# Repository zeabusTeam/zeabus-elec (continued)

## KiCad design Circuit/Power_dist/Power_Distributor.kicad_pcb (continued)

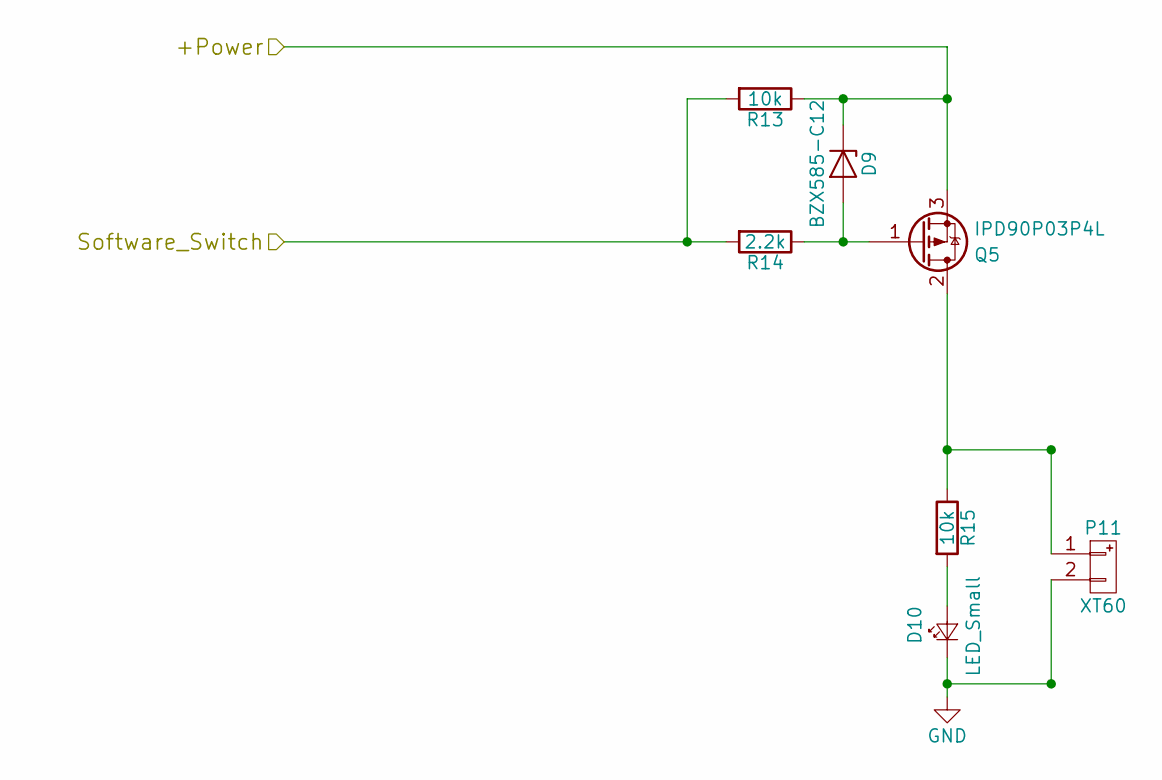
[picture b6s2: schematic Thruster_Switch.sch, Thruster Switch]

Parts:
D1: BZX585-C12; D_SOD-523
D2: LED_Small; LED_0603
P1: XT60
Q1: IPD90P03P4L; TO-252-2
R1, R3: 10k; R_0603
R2: 2.2k; R_0603

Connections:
+BATT: D1.1 (K), Q1.3 (S), R1.1; also elsewhere on the board
/Power_Controller/SW2_C: R1.2, R2.2; also elsewhere on the board
GND: D2.1 (K), P1.2; also elsewhere on the board
unnamed: D1.2 (A), Q1.1 (G), R2.1
unnamed: D2.2 (A), R3.2
unnamed: P1.1, Q1.2 (D), R3.1

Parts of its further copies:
D9: BZX585-C12; D_SOD-523
D10: LED_Small; LED_0603
P7, P11: XT60
Q4, Q5: IPD90P03P4L; TO-252-2
R13, R15: 10k; R_0603
R14: 2.2k; R_0603

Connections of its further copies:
+BATT: D9.1 (K), Q5.3 (S), R13.1; also elsewhere on the board
/Power_Controller/SW1_C: R13.2, R14.2; also elsewhere on the board
GND: D10.1 (K), P11.2; also elsewhere on the board
unnamed: D9.2 (A), Q5.1 (G), R14.1
unnamed: D10.2 (A), R15.2
unnamed: P11.1, Q5.2 (D), R15.1

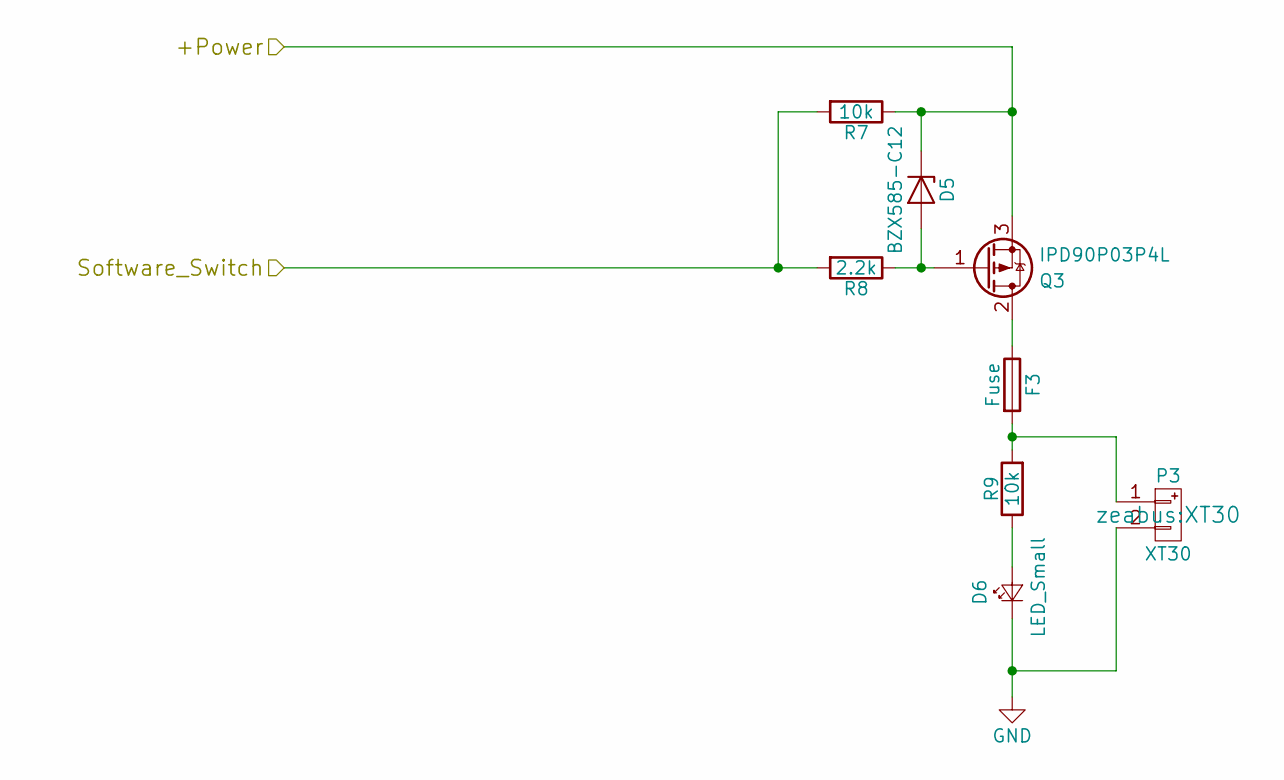
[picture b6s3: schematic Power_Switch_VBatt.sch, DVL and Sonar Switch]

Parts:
D3: BZX585-C12; D_SOD-523
D4: LED_Small; LED_0603_HandSoldering
F2: Fuse; FUSE_AUTO
P2: XT30
Q2: IPD90P03P4L; TO-252-2
R4, R6: 10k; R_0603
R5: 2.2k; R_0603

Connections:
+BATT: D3.1 (K), Q2.3 (S), R4.1; also elsewhere on the board
/Power_Controller/SW3_C: R4.2, R5.2; also elsewhere on the board
GND: D4.1 (K), P2.2; also elsewhere on the board
unnamed: D3.2 (A), Q2.1 (G), R5.1
unnamed: D4.2 (A), R6.1
unnamed: F2.1, Q2.2 (D)
unnamed: F2.2, P2.1, R6.2

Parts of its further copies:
D5: BZX585-C12; D_SOD-523
D6: LED_Small; LED_0603_HandSoldering
F3: Fuse; FUSE_AUTO
P3: XT30
Q3: IPD90P03P4L; TO-252-2
R7, R9: 10k; R_0603
R8: 2.2k; R_0603

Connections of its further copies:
+BATT: D5.1 (K), Q3.3 (S), R7.1; also elsewhere on the board
/Power_Controller/SW4_C: R7.2, R8.2; also elsewhere on the board
GND: D6.1 (K), P3.2; also elsewhere on the board
unnamed: D5.2 (A), Q3.1 (G), R8.1
unnamed: D6.2 (A), R9.1
unnamed: F3.1, Q3.2 (D)
unnamed: F3.2, P3.1, R9.2

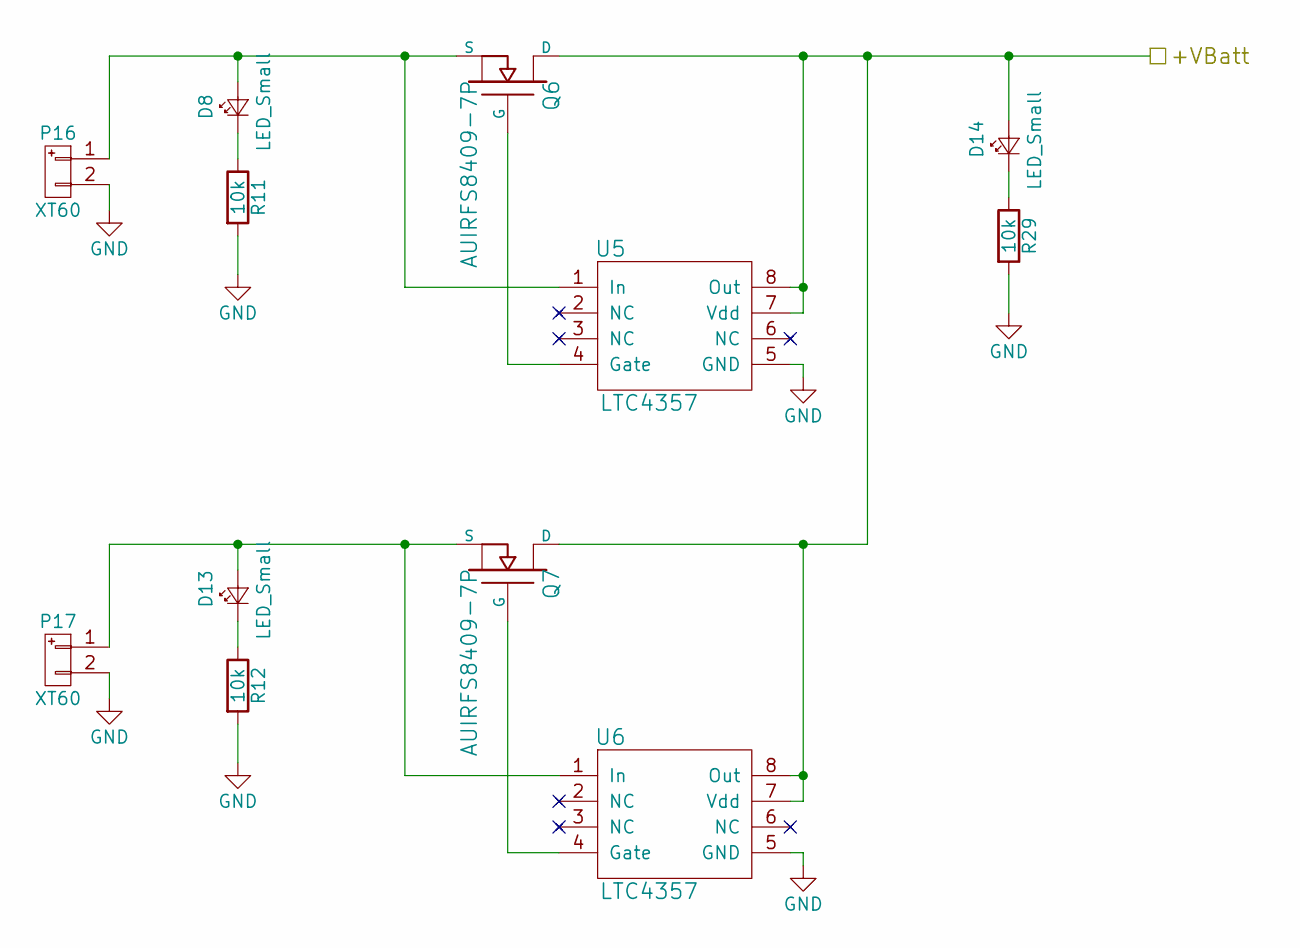
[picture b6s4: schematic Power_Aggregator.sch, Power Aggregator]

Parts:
D8, D13, D14: LED_Small; LED_0603_HandSoldering
P16, P17: XT60
Q6, Q7: AUIRFS8409-7P; D2PAK-7
R11, R12, R29: 10k; R_0603_HandSoldering
U5, U6: LTC4357; MSOP-8_3x3mm_Pitch0.65mm

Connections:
+BATT: D14.2 (A), Q6.D, Q7.D, U5.7 (Vdd), U5.8 (Out), U6.7 (Vdd), U6.8 (Out); also elsewhere on the board
GND: P16.2, P17.2, R11.2, R12.2, R29.2, U5.5 (GND), U6.5 (GND); also elsewhere on the board
unnamed: D8.1 (K), R11.1
unnamed: D8.2 (A), P16.1, Q6.S, U5.1 (In)
unnamed: D13.1 (K), R12.1
unnamed: D13.2 (A), P17.1, Q7.S, U6.1 (In)
unnamed: D14.1 (K), R29.1
unnamed: Q6.G, U5.4 (Gate)
unnamed: Q7.G, U6.4 (Gate)

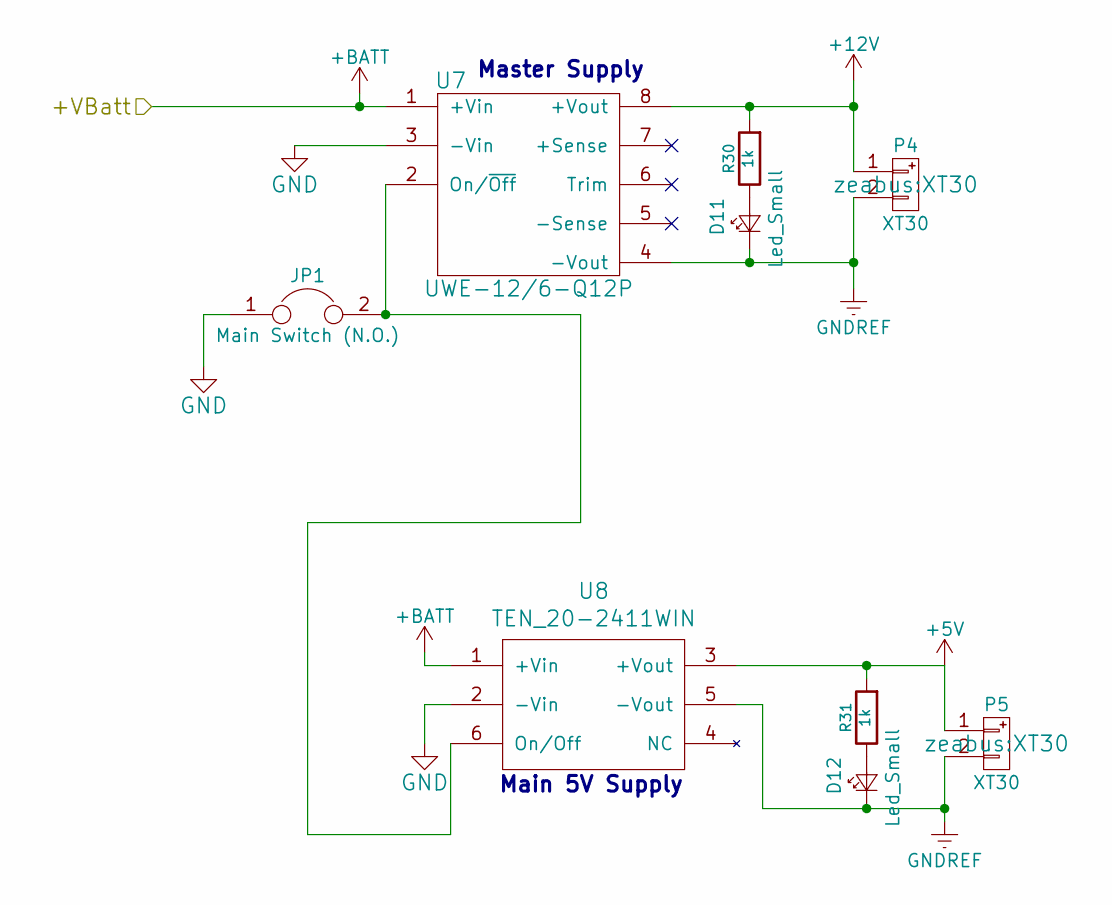
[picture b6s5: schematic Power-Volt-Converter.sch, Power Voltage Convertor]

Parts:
D11, D12: Led_Small; LED_0603_HandSoldering
JP1: Main Switch (N.O.); Pin_Header_Straight_1x02_Pitch2.54mm
P4, P5: XT30
R30, R31: 1k; R_0603_HandSoldering
U7: UWE-12/6-Q12P; UWE-xxxx
U8: TEN_20-2411WIN; TEN_20WIN

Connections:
+5V: P5.1, R31.2, U8.3 (+Vout); also elsewhere on the board
+12V: P4.1, R30.2, U7.8 (+Vout); also elsewhere on the board
+BATT: U7.1 (+Vin), U8.1 (+Vin); also elsewhere on the board
GND: JP1.1, U7.3 (-Vin), U8.2 (-Vin); also elsewhere on the board
GNDREF: D11.1 (K), D12.1 (K), P4.2, P5.2, U7.4 (-Vout), U8.5 (-Vout); also elsewhere on the board
unnamed: D11.2 (A), R30.1
unnamed: D12.2 (A), R31.1
unnamed: JP1.2, U7.2 (On/~Off), U8.6 (On/Off)

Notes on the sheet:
Master Supply
Main 5V Supply

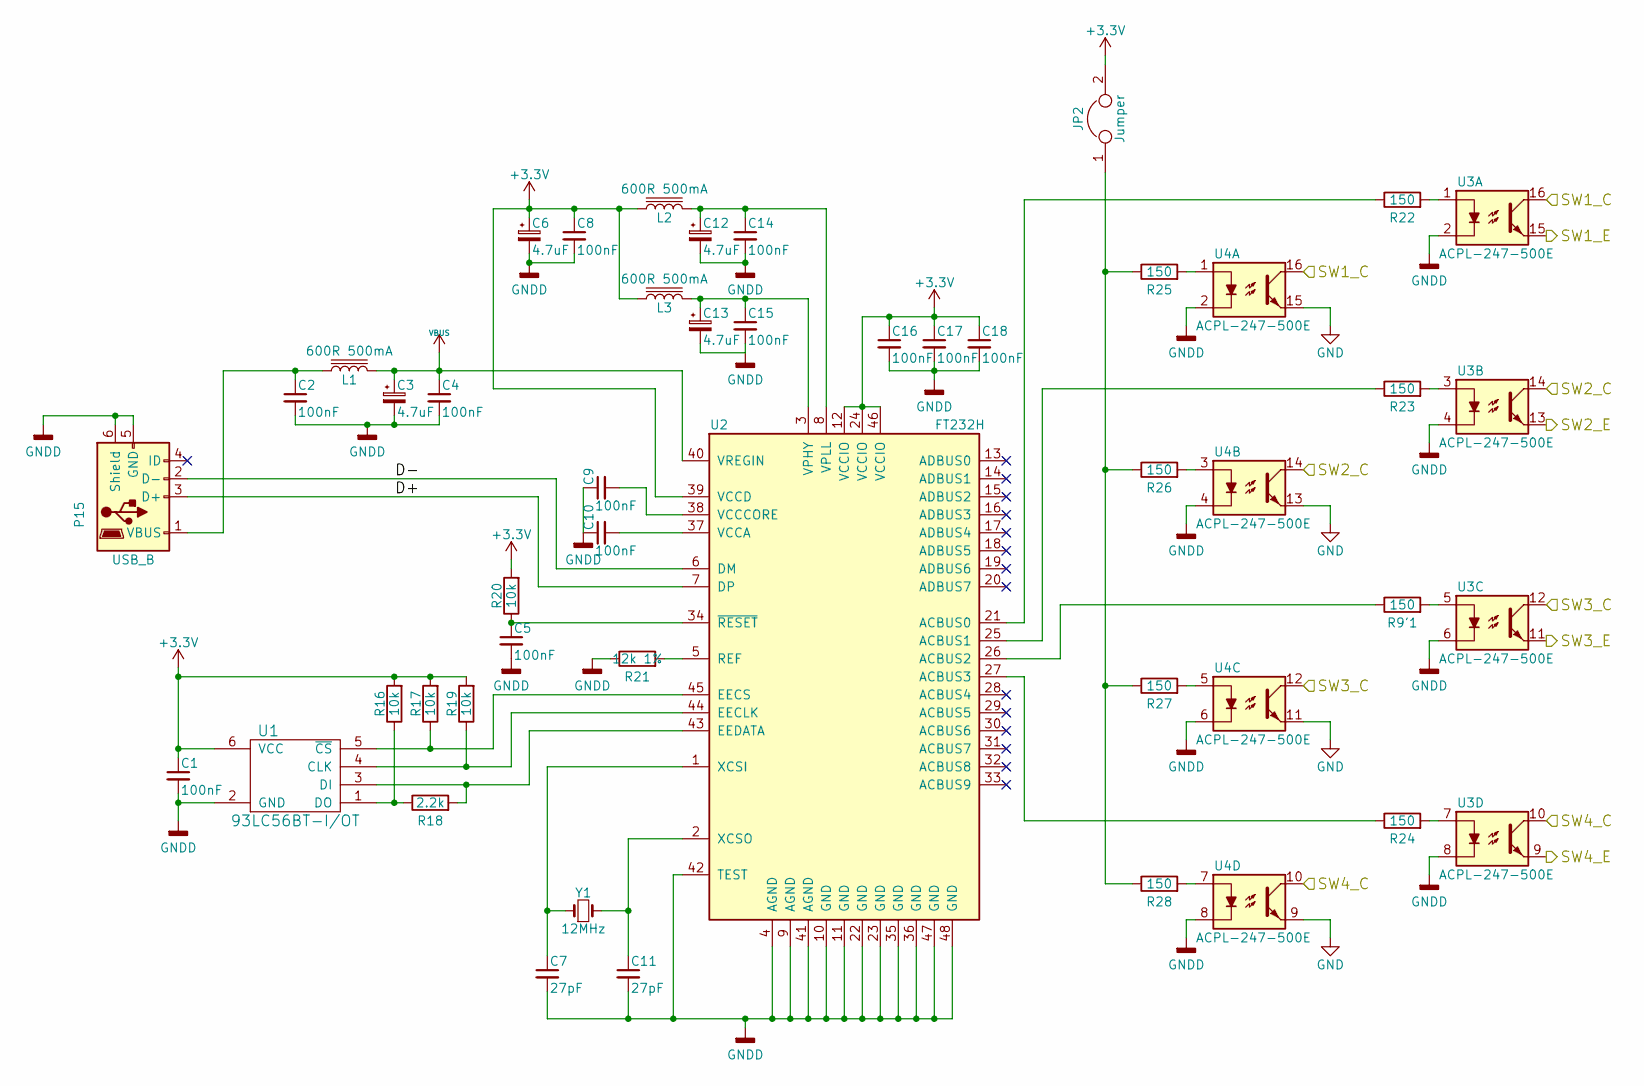
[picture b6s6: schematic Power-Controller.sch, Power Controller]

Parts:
C1, C2, C4, C5, C8, C9, C10, C14, C15, C16, C17, C18: 100nF; C_0603_HandSoldering
C3, C6, C12, C13: 4.7uF; C_0805_HandSoldering
C7, C11: 27pF; C_0603_HandSoldering
JP2: Jumper; Pin_Header_Straight_1x02_Pitch2.54mm
L1, L2, L3: 600R 500mA; C_0603_HandSoldering
P15: USB_B; USB_Mini-B
R9'1, R22, R23, R24, R25, R26, R27, R28: 150; R_0603_HandSoldering
R16, R17, R19, R20: 10k; R_0603_HandSoldering
R18: 2.2k; R_0603_HandSoldering
R21: 12k 1%; R_0603_HandSoldering
U1: 93LC56BT-I/OT; SOT-23-6
U2: FT232H; LQFP-48_7x7mm_Pitch0.5mm
U3, U4: ACPL-247-500E; SO16_4.4x10.3mm_Pitch1.27mm
Y1: 12MHz; Crystal_SMD_FOX_FE-2pin_7.5x5.0mm

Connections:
+3V3: C1.1, C6.1, C8.1, C16.1, C17.1, C18.1, JP2.2, L2.1, L3.1, R16.2, R17.2, R19.2, R20.2, U1.6 (VCC), U2.12 (VCCIO), U2.24 (VCCIO), U2.39 (VCCD), U2.46 (VCCIO)
/Kill_SW: U3.13, U3.15; also elsewhere on the board
/Power_Controller/SW1_C: U3.16, U4.16; also elsewhere on the board
/Power_Controller/SW2_C: U3.14, U4.14; also elsewhere on the board
/Power_Controller/SW3_C: U3.12, U4.12; also elsewhere on the board
/Power_Controller/SW4_C: U3.10, U4.10; also elsewhere on the board
D+: P15.3 (D+), U2.7 (DP); also elsewhere on the board
D-: P15.2 (D-), U2.6 (DM); also elsewhere on the board
GND: U3.9, U3.11, U4.9, U4.11, U4.13, U4.15; also elsewhere on the board
GNDD: C1.2, C2.2, C3.2, C4.2, C5.2, C6.2, C7.2, C8.2, C9.1, C10.1, C11.2, C12.2, C13.2, C14.2, C15.2, C16.2, C17.2, C18.2, P15.5 (GND), P15.6 (Shield), R21.1, U1.2 (GND), U2.4 (AGND), U2.9 (AGND), U2.10 (GND), U2.11 (GND), U2.22 (GND), U2.23 (GND), U2.35 (GND), U2.36 (GND), U2.41 (AGND), U2.42 (TEST), U2.47 (GND), U2.48 (GND), U3.2, U3.4, U3.6, U3.8, U4.2, U4.4, U4.6, U4.8; also elsewhere on the board
unnamed: C2.1, L1.1, P15.1 (VBUS)
unnamed: C5.1, R20.1, U2.34 (~RESET)
unnamed: C7.1, U2.1 (XCSI), Y1.1
unnamed: C9.2, U2.38 (VCCCORE)
unnamed: C10.2, U2.37 (VCCA)
unnamed: C11.1, U2.2 (XCSO), Y1.2
unnamed: C12.1, C14.1, L2.2, U2.8 (VPLL)
unnamed: C13.1, C15.1, L3.2, U2.3 (VPHY)
unnamed: JP2.1, R25.1, R26.1, R27.1, R28.1
unnamed: R9'1.1, U2.26 (ACBUS2)
unnamed: R9'1.2, U3.5
unnamed: R16.1, R18.1, U1.1 (DO)
unnamed: R17.1, U1.5 (~CS), U2.45 (EECS)
unnamed: R18.2, U1.3 (DI), U2.43 (EEDATA)
unnamed: R19.1, U1.4 (CLK), U2.44 (EECLK)
unnamed: R21.2, U2.5 (REF)
unnamed: R22.1, U2.21 (ACBUS0)
unnamed: R22.2, U3.1
unnamed: R23.1, U2.25 (ACBUS1)
unnamed: R23.2, U3.3
unnamed: R24.1, U2.27 (ACBUS3)
unnamed: R24.2, U3.7
unnamed: R25.2, U4.1
unnamed: R26.2, U4.3
unnamed: R27.2, U4.5
unnamed: R28.2, U4.7
VBUS: C3.1, C4.1, L1.2, U2.40 (VREGIN); also elsewhere on the board

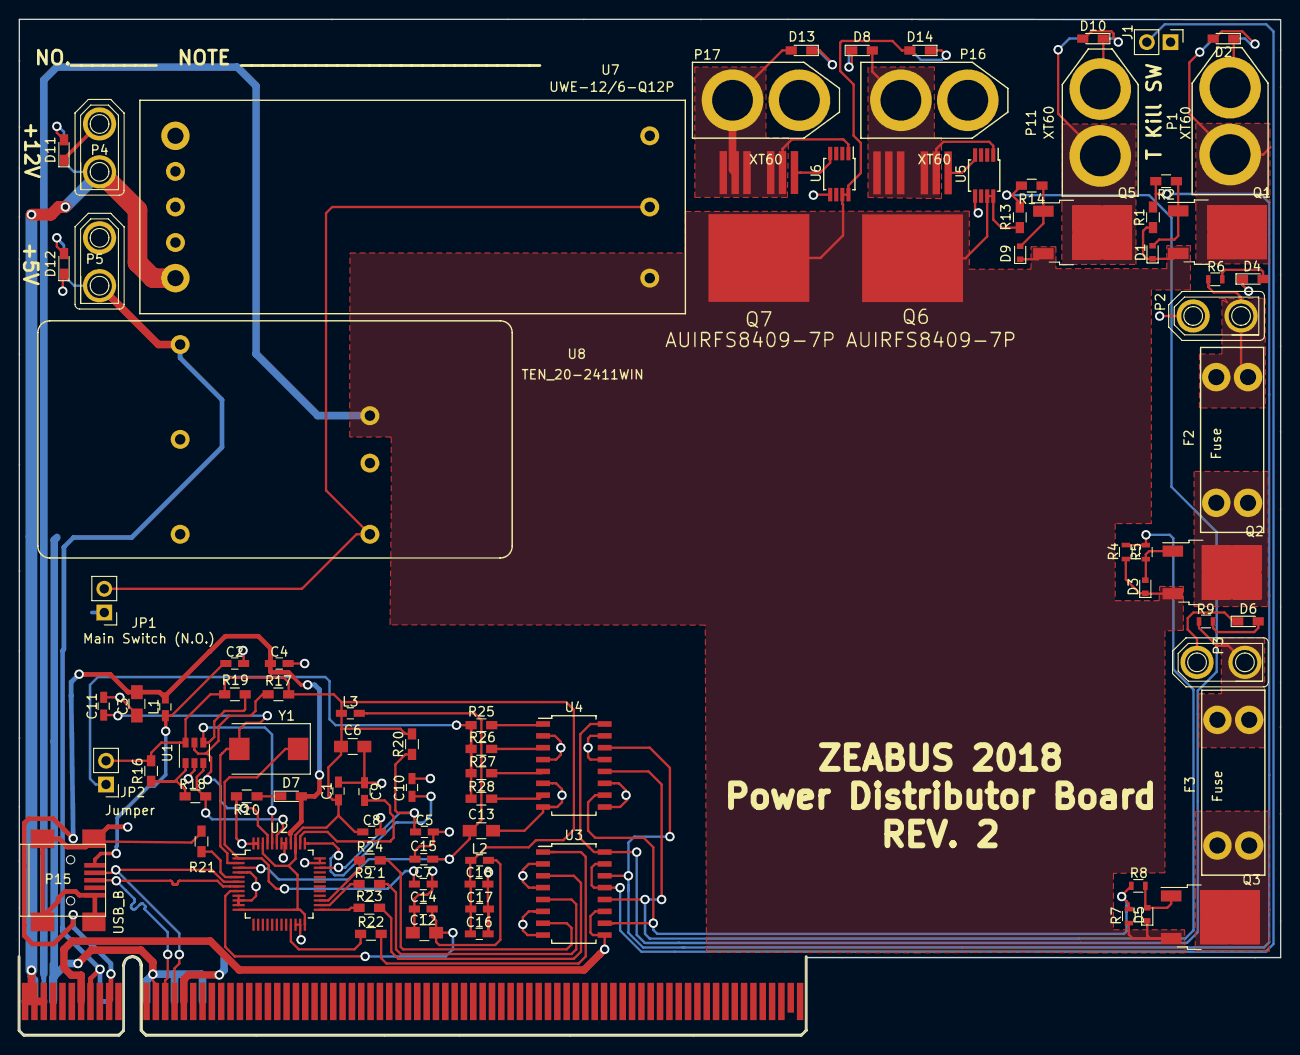
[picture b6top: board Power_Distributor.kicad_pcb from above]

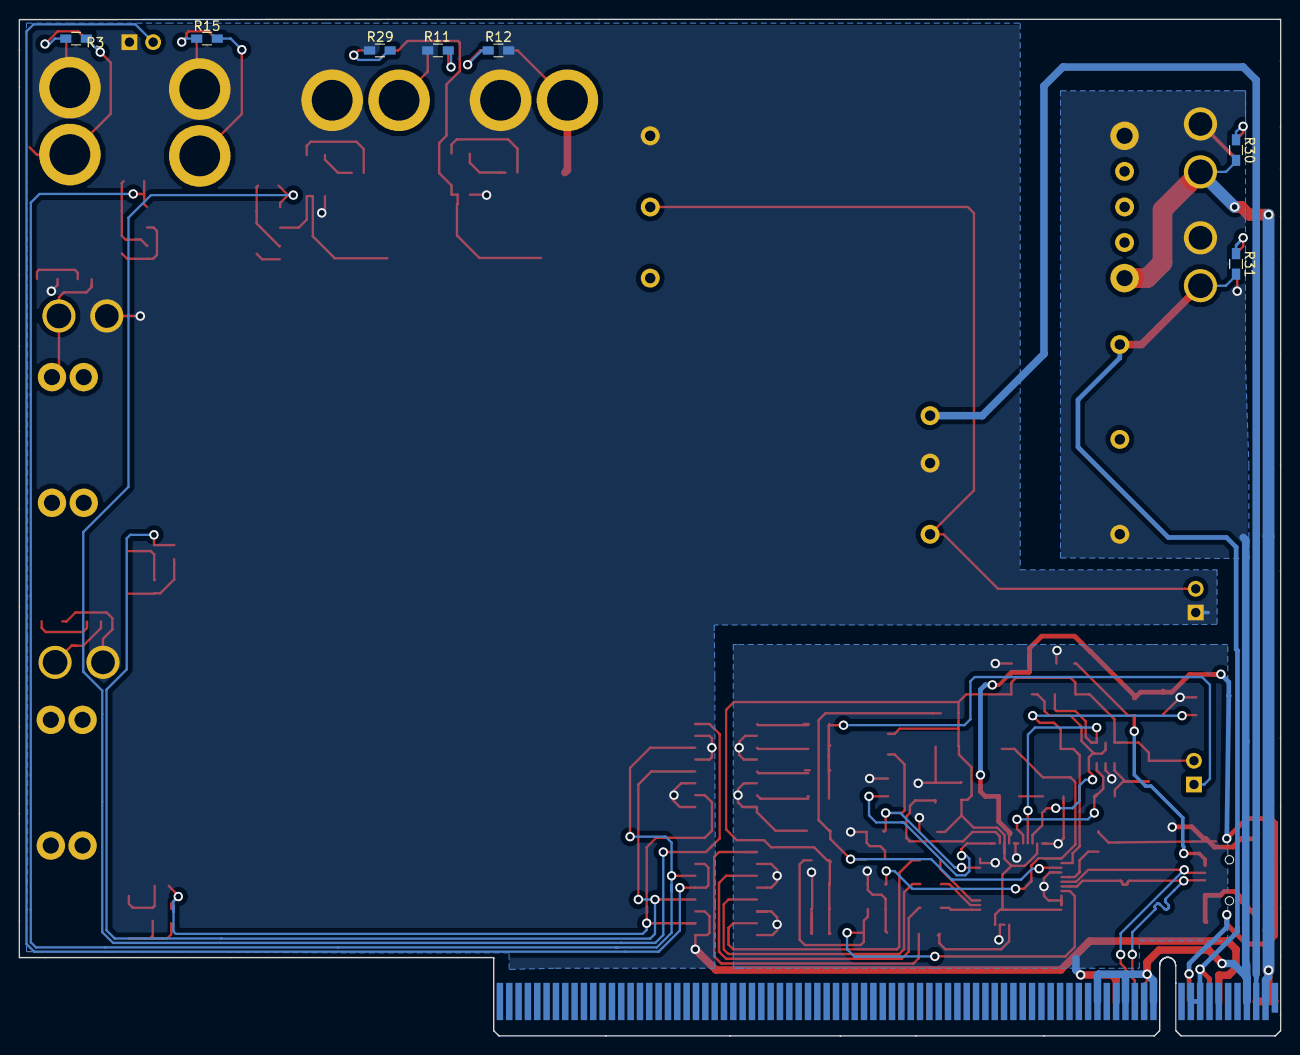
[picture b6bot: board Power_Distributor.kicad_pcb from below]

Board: 2 copper layers, 135.1 x 108.9 mm, 97 parts (7 on the bottom side), 66 nets.

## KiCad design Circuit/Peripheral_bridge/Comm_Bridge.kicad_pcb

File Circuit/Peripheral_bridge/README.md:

# Zeabus-Elec-2017-Peripheral_bridge
## Use relative path to ../Kicad-Libraries for specific components
Bridge circuit for several peripherals. It communicates to NUC via a USB (through USB hub). The specifications are:
1. Use 5V power from USB connector
2. Has 2 **isolated** RS-232 ports (use ADM3251E as the tranceiver/receiver) for:
 * DSP board
 * DVL board
3. Has an analog input and a 5V power-supply for a presure sensor.
4. Has 8-channel digital output with **opto-isolator** for solinoid valves.

Because this module has many sub-modules, there are several subscriber and publisher topics links to this module. Sub-modules are:
1. Solenoid-valve switches
2. Barometer
3. Rs-232 Communication channel 1
4. Rs-232 Communication channel 2

The diagram of these sub-modules (each of them can be cosidered as a node) is as:

<pre>
+------------------+
|                  |-------- /zeabus/elec/barometer ------&gt;
| Barometer        |
|                  |-----+
+------------------+     |
                         |
+------------------+     |
|                  |&lt;------ /zeabus/elec/solenoid_sw -----
| Solenoid Switches|     |
|                  |-----+
+------------------+     |
                         +--- /zeabus/elec/hw_error ------&gt;
+------------------+     |
|                  |-----+ 
| RS-232 Channel 1 |&lt;------ /zeabus/elec/comm1/send ------
|                  |---------- /zeabus/elec/comm1/recv ---&gt;
+------------------+     |
                         |
+------------------+     |
|                  |-----+
| RS-232 Channel 2 |&lt;------ /zeabus/elec/comm2/send ------
|                  |---------- /zeabus/elec/comm1/recv ---&gt;
+------------------+
</pre>

The topic **/zeabus/elec/hw_error** is commonly used among all nodes and modules (including the Power Distributor) to announce error messages of the modules.

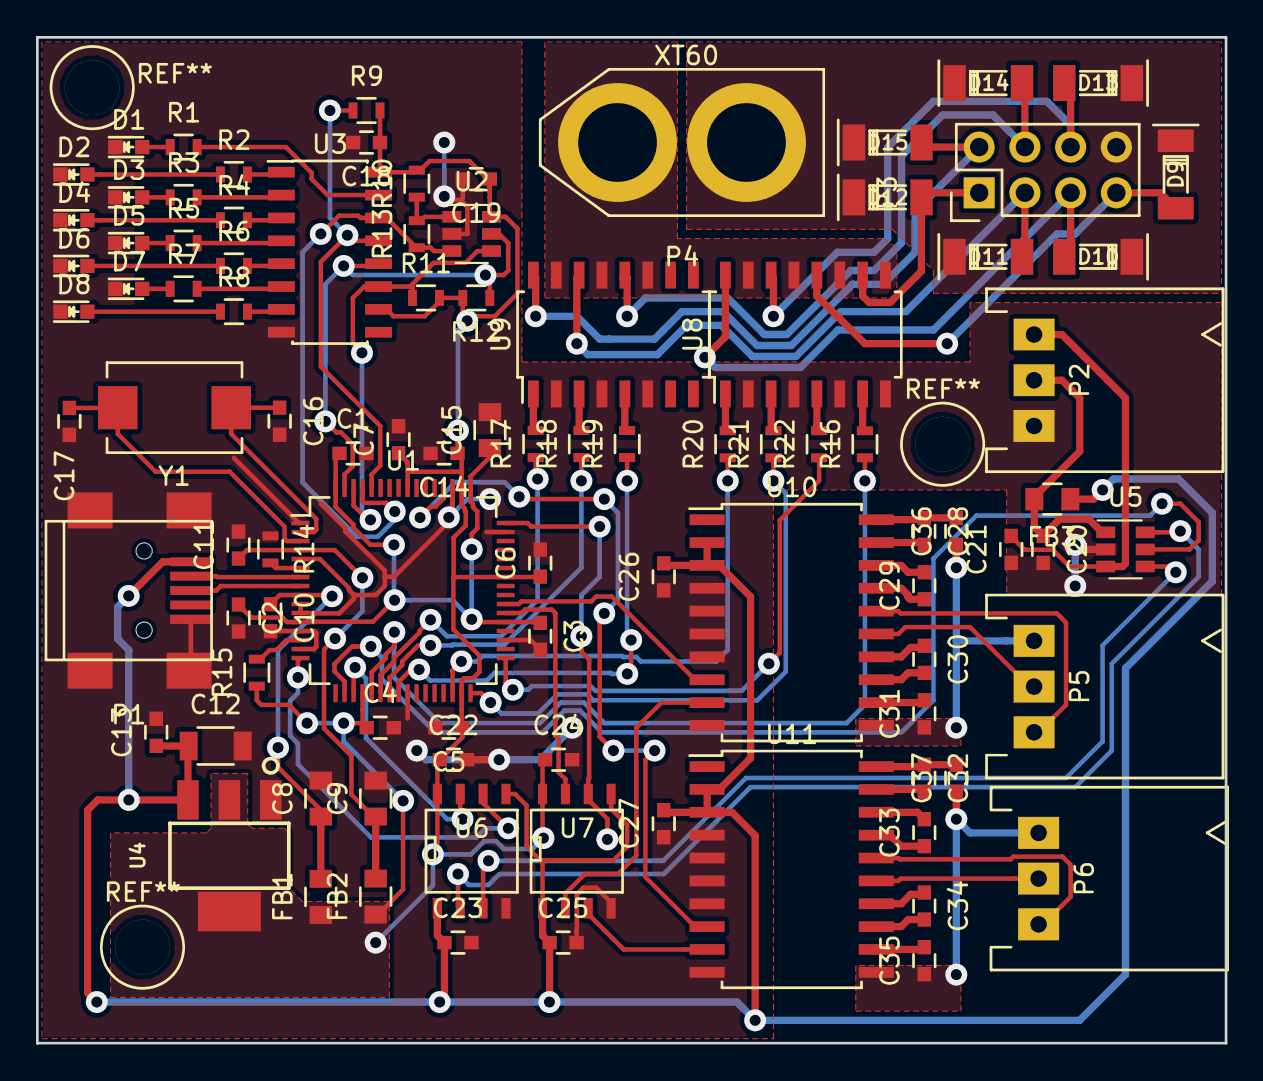
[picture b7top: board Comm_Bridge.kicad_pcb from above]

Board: 2 copper layers, 66.0 x 55.9 mm, 95 parts (0 on the bottom side), 89 nets.

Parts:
C1, C2, C3, C4, C5, C6, C7, C10, C11, C13, C14, C18, C19, C20, C21, C22, C23, C24, C25, C26, C27, C28, C29, C30, C31, C32, C33, C34, C35, C36, C37: 100nF; C_0603
C8, C9: 4.7uF; C_0805
C12: 10uF; C_1206
C15: 3.3uF; C_0805
C16, C17: 27pF; C_0603
D1, D2, D3, D4, D5, D6, D7, D8: LED; LED_0603
D9, D10, D11, D12, D13, D14, D15: FDLL4148; SOD-80
FB1, FB2, FB3: 600R 0.5A; C_0805
P1: USB_B; USB_Mini-B
P2, P5, P6: CONN_01X03; 90136-2013
P3: Solenoid; Pin_Header_Straight_2x04
P4: XT60
R1, R2, R3, R4, R5, R6, R7, R8: 330; R_0603
R9, R10, R11, R12, R15: 10k; R_0603
R13: 2.2k; R_0603
R14: 12k 1%; R_0603
R16, R17, R18, R19, R20, R21, R22: 150; R_0603
U1: FT4232H; LQFP-64_10x10mm_Pitch0.5mm
U2: 93LC56BT-I/OT; SOT-23-6
U3: 74HC595_CUST; SOIC-16_3.9x9.9mm_Pitch1.27mm
U4: LM1117-XX; SOT223
U5: ADC101S021; SOT-23-6
U6, U7: NLSX4373; SOIC-8-N
U8, U9: ACPL-247-500E; SO16_4.4x10.3mm_Pitch1.27mm
U10, U11: ADM3251E; SOIC-20W_7.5x12.8mm_Pitch1.27mm
Y1: 12MHz; Crystal_FOX-FE_SMD

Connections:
+1V8: C1.1, C2.1, C3.1, C15.1, U1.12, U1.37, U1.49, U1.64
+3V3: C4.1, C5.1, C6.1, C7.1, C14.1, C18.1, C19.1, C22.1, C24.1, FB1.1, FB2.1, R9.2, R10.2, R11.2, R12.2, R15.1, U1.20, U1.31, U1.42, U1.50, U1.56, U2.6, U3.10, U3.16, U4.2, U4.4, U6.8, U7.8
+12V: D9.1, D10.1, D11.1, D12.1, D13.1, D14.1, D15.1, P3.8, P4.1
/Sol1: D12.2, P3.1, U8.10
/Sol2: D15.2, P3.2, U9.16
/Sol3: D11.2, P3.3, U9.14
/Sol4: D14.2, P3.4, U9.12
/Sol5: D10.2, P3.5, U8.16
/Sol6: D13.2, P3.6, U8.14
/Sol7: D9.2, P3.7, U8.12
GND: C1.2, C2.2, C3.2, C4.2, C5.2, C6.2, C7.2, C8.2, C9.2, C10.2, C11.2, C12.2, C13.2, C14.2, C15.2, C16.2, C17.2, C18.2, C19.2, C20.2, C21.1, C22.2, C23.2, C24.2, C25.2, C26.1, C27.1, D1.1, D2.1, D3.1, D4.1, D5.1, D6.1, D7.1, D8.1, P1.5, P1.6, P2.3, R14.1, U1.1, U1.5, U1.10, U1.11, U1.13, U1.15, U1.25, U1.35, U1.47, U1.51, U2.2, U3.8, U4.1, U5.2, U6.4, U7.4, U8.2, U8.4, U8.6, U8.8, U9.2, U9.4, U9.6, U10.4, U10.5, U10.6, U10.7, U10.10, U11.4, U11.5, U11.6, U11.7, U11.10
GNDPWR: P4.2, U8.9, U8.11, U8.13, U8.15, U9.11, U9.13, U9.15
unnamed: C8.1, C10.1, FB1.2, U1.9
unnamed: C9.1, C11.1, FB2.2, U1.4
unnamed: C16.1, U1.2, Y1.1
unnamed: C17.1, U1.3, Y1.2
unnamed: C20.1, FB3.2, P2.2, U5.1
unnamed: C21.2, P2.1, U5.3
unnamed: C28.1, C36.2, U10.20
unnamed: C28.2, U10.19
unnamed: C29.1, U10.17
unnamed: C29.2, U10.18
unnamed: C30.1, U10.14
unnamed: C30.2, U10.13
unnamed: C31.1, C36.1, P5.1, U10.11
unnamed: C31.2, U10.12
unnamed: C32.1, C37.2, U11.20
unnamed: C32.2, U11.19
unnamed: C33.1, U11.17
unnamed: C33.2, U11.18
unnamed: C34.1, U11.14
unnamed: C34.2, U11.13
unnamed: C35.1, C37.1, P6.1, U11.11
unnamed: C35.2, U11.12
unnamed: D1.2, R1.1
unnamed: D2.2, R2.1
unnamed: D3.2, R3.1
unnamed: D4.2, R4.1
unnamed: D5.2, R5.1
unnamed: D6.2, R6.1
unnamed: D7.2, R7.1
unnamed: D8.2, R8.1
unnamed: P1.2, U1.7
unnamed: P1.3, U1.8
unnamed: P5.2, U10.15
unnamed: P5.3, U10.16
unnamed: P6.2, U11.15
unnamed: P6.3, U11.16
unnamed: R1.2, U3.15
unnamed: R2.2, U3.1
unnamed: R3.2, U3.2
unnamed: R4.2, U3.3
unnamed: R5.2, U3.4
unnamed: R6.2, U3.5
unnamed: R7.2, U3.6
unnamed: R8.2, U3.7
unnamed: R9.1, U1.60, U3.13
unnamed: R10.1, R13.2, U2.1
unnamed: R11.1, U1.62, U2.4, U3.11
unnamed: R12.1, U1.63, U2.5, U3.12
unnamed: R13.1, U1.61, U2.3, U3.14
unnamed: R14.2, U1.6
unnamed: R15.2, U1.14
unnamed: R16.1, U1.21
unnamed: R16.2, U8.7
unnamed: R17.1, U1.22
unnamed: R17.2, U9.1
unnamed: R18.1, U1.23
unnamed: R18.2, U9.3
unnamed: R19.1, U1.24
unnamed: R19.2, U9.5
unnamed: R20.1, U1.30
unnamed: R20.2, U8.1
unnamed: R21.1, U1.32
unnamed: R21.2, U8.3
unnamed: R22.1, U1.33
unnamed: R22.2, U8.5
unnamed: U1.16, U6.6
unnamed: U1.18, U5.5
unnamed: U1.19, U6.7
unnamed: U1.38, U7.7
unnamed: U1.39, U10.8
unnamed: U1.48, U7.6
unnamed: U1.52, U11.8
unnamed: U5.4, U6.3
unnamed: U5.6, U6.2
unnamed: U7.2, U10.9
unnamed: U7.3, U11.9
VBUS: C12.1, C13.1, C23.1, C25.1, C26.2, C27.2, FB3.1, P1.1, U4.3, U6.1, U6.5, U7.1, U7.5, U10.2, U10.3, U11.2, U11.3

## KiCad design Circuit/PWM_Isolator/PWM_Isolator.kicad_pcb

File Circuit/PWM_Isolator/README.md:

# Zeabus-Elec-PWM_Isolator
A logic isolator coupled between the Pololu RC controller and motor drivers. The specifications are:

1. Use __Si8660BA-B-IS1__ (Narrow SOIC package) as the isolator. The reason of choosing this type of isolator is low current consumption.
2. Support 12 Channels of PWM signal.
2. The board should have the same size as Pololu Maestro 12-Channel RC Servo Controller and be able to plug to the Pololu as an add-on.
3. VDD1 is taken directly from Pololu
4. VDD2 is selectable from one of the 12 motor drivers.

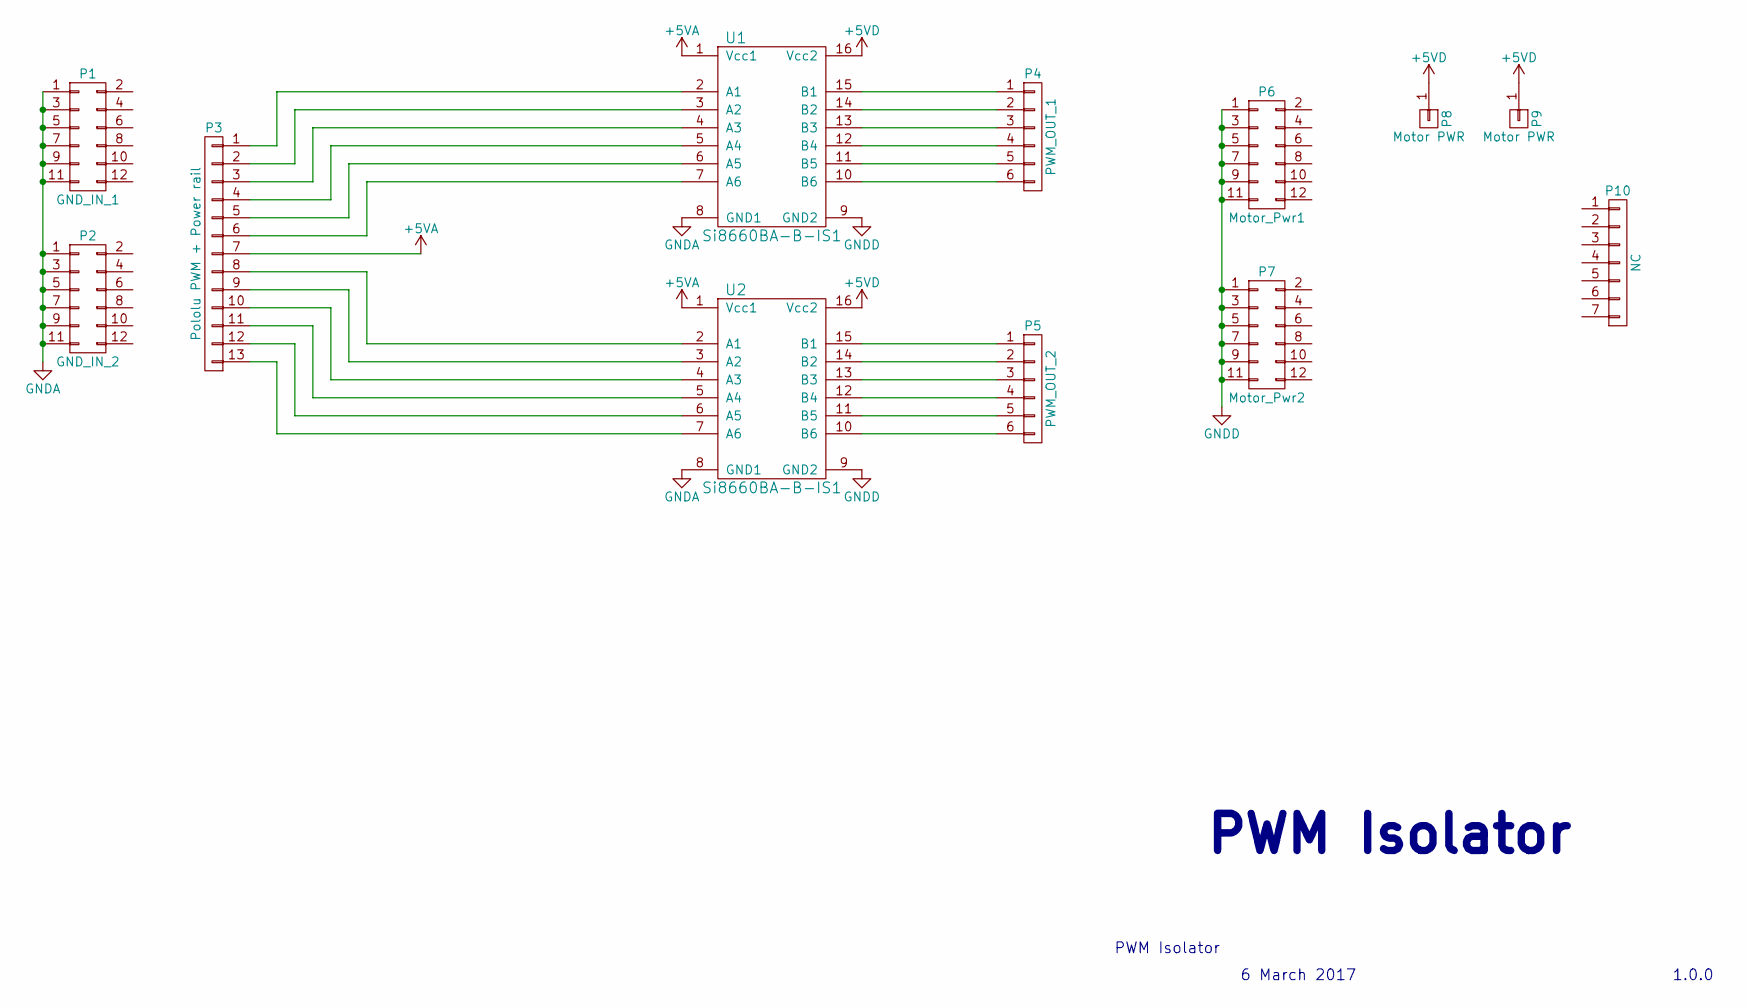
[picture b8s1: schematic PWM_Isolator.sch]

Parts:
P1: GND_IN_1; Socket_Strip_Straight_2x06
P2: GND_IN_2; Socket_Strip_Straight_2x06
P3: Pololu PWM + Power rail; Socket_Strip_Straight_1x13
P4: PWM_OUT_1; Pin_Header_Straight_1x06
P5: PWM_OUT_2; Pin_Header_Straight_1x06
P6: Motor_Pwr1; Pin_Header_Straight_2x06
P7: Motor_Pwr2; Pin_Header_Straight_2x06
P8, P9: Motor PWR; Pin_Header_Straight_1x01
P10: NC; Socket_Strip_Straight_1x07
U1, U2: Si8660BA-B-IS1; Narrow-SOIC-16

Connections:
+5VA: P3.7, U1.1 (Vcc1), U2.1 (Vcc1)
+5VD: P8.1, P9.1, U1.16 (Vcc2), U2.16 (Vcc2)
GNDA: P1.1, P1.3, P1.5, P1.7, P1.9, P1.11, P2.1, P2.3, P2.5, P2.7, P2.9, P2.11, U1.8 (GND1), U2.8 (GND1)
GNDD: P6.1, P6.3, P6.5, P6.7, P6.9, P6.11, P7.1, P7.3, P7.5, P7.7, P7.9, P7.11, U1.9 (GND2), U2.9 (GND2)
unnamed: P3.1, U1.2 (A1)
unnamed: P3.2, U1.3 (A2)
unnamed: P3.3, U1.4 (A3)
unnamed: P3.4, U1.5 (A4)
unnamed: P3.5, U1.6 (A5)
unnamed: P3.6, U1.7 (A6)
unnamed: P3.8, U2.2 (A1)
unnamed: P3.9, U2.3 (A2)
unnamed: P3.10, U2.4 (A3)
unnamed: P3.11, U2.5 (A4)
unnamed: P3.12, U2.6 (A5)
unnamed: P3.13, U2.7 (A6)
unnamed: P4.1, U1.15 (B1)
unnamed: P4.2, U1.14 (B2)
unnamed: P4.3, U1.13 (B3)
unnamed: P4.4, U1.12 (B4)
unnamed: P4.5, U1.11 (B5)
unnamed: P4.6, U1.10 (B6)
unnamed: P5.1, U2.15 (B1)
unnamed: P5.2, U2.14 (B2)
unnamed: P5.3, U2.13 (B3)
unnamed: P5.4, U2.12 (B4)
unnamed: P5.5, U2.11 (B5)
unnamed: P5.6, U2.10 (B6)

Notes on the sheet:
PWM Isolator
6 March 2017
1.0.0

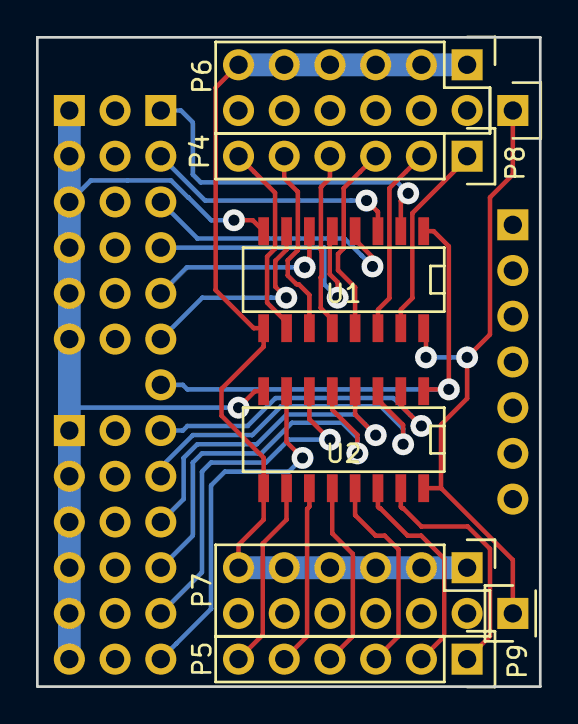
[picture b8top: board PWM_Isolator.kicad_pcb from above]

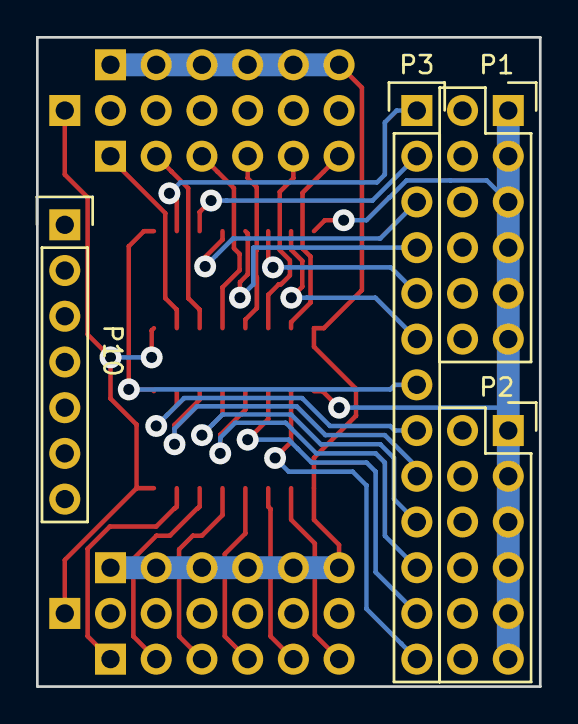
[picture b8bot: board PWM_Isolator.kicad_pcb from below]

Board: 2 copper layers, 27.9 x 36.1 mm, 12 parts (4 on the bottom side), 28 nets.
